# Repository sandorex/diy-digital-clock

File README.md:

# diy-digital-clock
DIY LED segment clock using DS1302 and ATTiny13a, with shift registers

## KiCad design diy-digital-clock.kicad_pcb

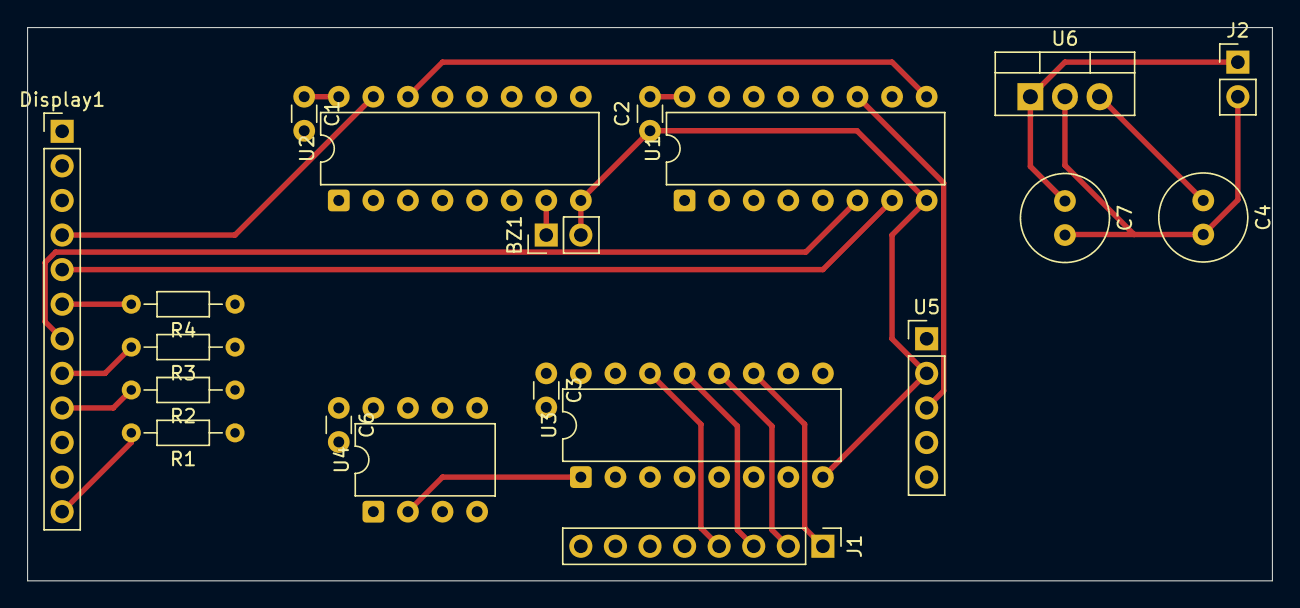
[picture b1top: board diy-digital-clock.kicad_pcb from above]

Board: 10 copper layers, 91.4 x 40.6 mm, 20 parts (0 on the bottom side), 34 nets.

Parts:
BZ1: Buzzer; PinHeader_1x02_P2.54mm_Vertical
C1, C2, C3, C6: 100nf; C_Disc_D3.0mm_W1.6mm_P2.50mm
C4, C7: 100uf; C_Radial_D6.3mm_H5.0mm_P2.50mm
Display1: PinHeader_1x12_P2.54mm_Vertical
J1: INPUT; PinHeader_1x08_P2.54mm_Vertical
J2: DC IN; PinHeader_1x02_P2.54mm_Vertical
R1, R2, R3, R4: 1K; R_Axial_DIN0204_L3.6mm_D1.6mm_P7.62mm_Horizontal
U1, U2: 74AHC595; DIP-16_W7.62mm
U3: 74HC165; DIP-16_W7.62mm
U4: ATtiny13A-P; DIP-8_W7.62mm
U5: DS1302; PinHeader_1x05_P2.54mm_Vertical
U6: LM7805_TO220; TO-220-3_Vertical

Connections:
+5V: C1.1, C2.2, C3.1, C4.1, C6.1, U1.16 (VCC), U2.16 (VCC), U3.16 (VCC), U4.8 (VCC), U5.1 (VCC), U6.3 (VO)
+VDC: C7.1, J2.1, U6.1 (VI)
/OUTPUT0: R1.1, U1.15 (QA)
/OUTPUT1: R2.1, U1.1 (QB)
/OUTPUT2: R3.1, U1.2 (QC)
/OUTPUT3: R4.1, U1.3 (QD)
/OUTPUT4: Display1.11 (a), U1.4 (QE)
/OUTPUT5: Display1.10 (f), U1.5 (QF)
/OUTPUT6: Display1.7 (b), U1.6 (QG)
/OUTPUT7: Display1.5 (g), U1.7 (QH)
/OUTPUT8: Display1.4 (c), U2.15 (QA)
/OUTPUT9: Display1.3 (DD), U2.1 (QB)
/OUTPUT10: Display1.2 (d), U2.2 (QC)
/OUTPUT11: Display1.1 (e), U2.3 (QD)
/OUTPUT15: BZ1.1 (+), U2.7 (QH)
CLOCK: U1.11 (SRCLK), U2.11 (SRCLK), U3.2 (CP), U4.6 (PB1), U5.3 (CLK)
DATA: U1.14 (SER), U3.9 (Q7), U4.5 (PB0), U5.4 (DATA)
DS_CE: U4.3 (PB4), U5.5 (RST/CE)
GND: BZ1.2 (-), C1.2, C2.1, C3.2, C4.2, C6.2, C7.2, J2.2, U1.8 (GND), U2.8 (GND), U3.8 (GND), U4.4 (GND), U5.2 (GND), U6.2 (GND)
unnamed: Display1.12 (D_{1}), R1.2
unnamed: Display1.9 (D_{2}), R2.2
unnamed: Display1.8 (D_{3}), R3.2
unnamed: Display1.6 (D_{4}), R4.2
unnamed: J1.1, U3.11 (D0)
unnamed: J1.2, U3.12 (D1)
unnamed: J1.3, U3.13 (D2)
unnamed: J1.4, U3.14 (D3)
unnamed: J1.5, U3.3 (D4)
unnamed: J1.6, U3.4 (D5)
unnamed: J1.7, U3.5 (D6)
unnamed: J1.8, U3.6 (D7)
unnamed: U1.9 (QH'), U2.14 (SER)
OUT_RCLOCK: U1.12 (RCLK), U2.12 (RCLK), U4.7 (PB2)
~INPUT_LD: U3.1 (~PL), U4.2 (PB3)

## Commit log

2025-03-15 WIP schematic and protoboard PCB
    Very much work in progress
